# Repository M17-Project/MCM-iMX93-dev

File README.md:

[![CC BY-NC-SA 4.0][cc-by-nc-sa-shield]][cc-by-nc-sa]

# MCM-iMX93-dev
MCM-iMX93 System on Module development board.

## License
This work is licensed under a
[Creative Commons Attribution-NonCommercial-ShareAlike 4.0 International License][cc-by-nc-sa].

[![CC BY-NC-SA 4.0][cc-by-nc-sa-image]][cc-by-nc-sa]

[cc-by-nc-sa]: http://creativecommons.org/licenses/by-nc-sa/4.0/
[cc-by-nc-sa-image]: https://licensebuttons.net/l/by-nc-sa/4.0/88x31.png
[cc-by-nc-sa-shield]: https://img.shields.io/badge/License-CC%20BY--NC--SA%204.0-lightgrey.svg

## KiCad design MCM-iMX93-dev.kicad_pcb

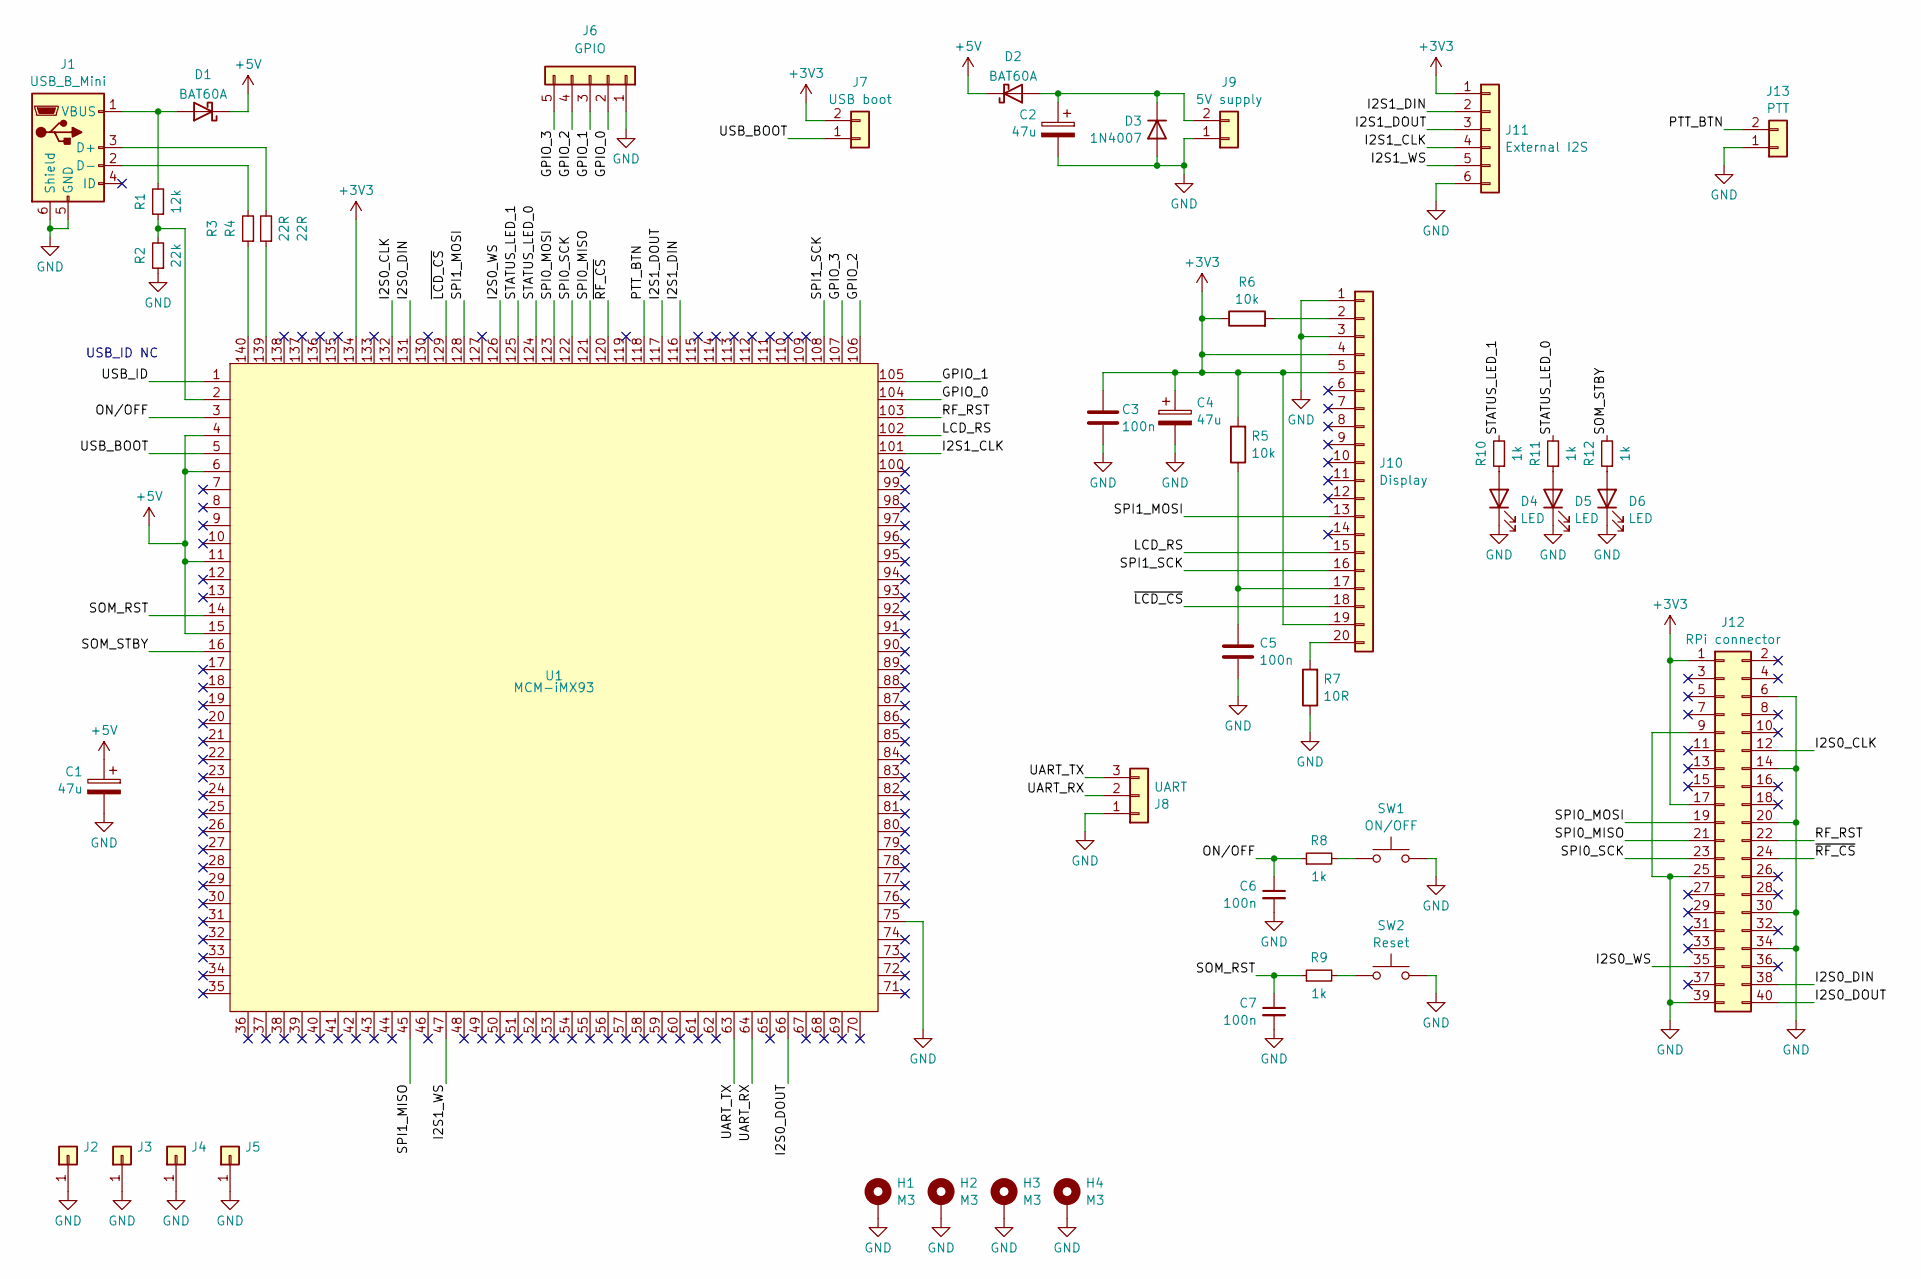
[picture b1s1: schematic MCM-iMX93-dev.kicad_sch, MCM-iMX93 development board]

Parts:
C1, C2, C4: 47u; C_Radial_D4.0mm_H5.0mm_P1.50mm
C3, C5: 100n; C_0603_1608Metric_Pad1.08x0.95mm_HandSolder
C6, C7: 100n; C_0603_1608Metric_Pad1.08x0.95mm_HandSolder; MPN C0603C104M5RAC7411
D1, D2: BAT60A; D_SOD-323; MPN Generic Schottky/10Vr/2A/SOD323-2; LCSC Part # C520634
D3: 1N4007; D_DO-41_SOD81_P10.16mm_Horizontal
D4, D5, D6: LED; LED_0603_1608Metric
H1, H2, H3, H4: M3; MountingHole_3.2mm_M3_DIN965_Pad
J1: USB_B_Mini; USB_Mini-B_Lumberg_2486_01_Horizontal
J2, J3, J4, J5: TestPoint_Pad_3.0x3.0mm
J6: GPIO; PinHeader_1x05_P2.54mm_Vertical
J7: USB boot; PinHeader_1x02_P2.54mm_Vertical
J8: UART; PinHeader_1x03_P2.54mm_Vertical
J9: 5V supply; PinHeader_1x02_P2.54mm_Vertical
J10: Display; 20x0.6_ribbon
J11: External I2S; PinHeader_1x06_P2.54mm_Vertical
J12: RPi connector; PinHeader_2x20_P2.54mm_Vertical
J13: PTT; PinHeader_1x02_P2.54mm_Vertical
R1: 12k; R_0603_1608Metric_Pad0.98x0.95mm_HandSolder
R2: 22k; R_0603_1608Metric_Pad0.98x0.95mm_HandSolder
R3, R4: 22R; R_0603_1608Metric_Pad0.98x0.95mm_HandSolder
R5, R6: 10k; R_0603_1608Metric_Pad0.98x0.95mm_HandSolder
R7: 10R; R_0603_1608Metric_Pad0.98x0.95mm_HandSolder
R8, R9, R10, R11, R12: 1k; R_0603_1608Metric_Pad0.98x0.95mm_HandSolder
SW1: ON/OFF; SW_PUSH_6mm
SW2: Reset; SW_PUSH_6mm
U1: MCM-iMX93; QFN-140_hole_small

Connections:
+3V3: C3.1, C4.1, J7.2, J10.4, J10.5, J10.19, J11.1, J12.1, J12.17, R5.2, R6.1, U1.134
+5V: C1.1, D1.1 (K), D2.1 (K), U1.4, U1.6, U1.11, U1.15
/GPIO_0: J6.2, U1.104
/GPIO_1: J6.3, U1.105
/GPIO_2: J6.4, U1.106
/GPIO_3: J6.5, U1.107
/I2S0_CLK: J12.12, U1.132
/I2S0_DIN: J12.38, U1.131
/I2S0_DOUT: J12.40, U1.66
/I2S0_WS: J12.35, U1.126
/I2S1_CLK: J11.4, U1.101
/I2S1_DIN: J11.2, U1.116
/I2S1_DOUT: J11.3, U1.117
/I2S1_WS: J11.5, U1.47
/LCD_RS: J10.15, U1.102
/ON/OFF: C6.1, R8.1, U1.3
/PTT_BTN: J13.2, U1.118
/RF_RST: J12.22, U1.103
/SOM_RST: C7.1, R9.1, U1.14
/SOM_STBY: R12.2, U1.16
/SPI0_MISO: J12.21, U1.121
/SPI0_MOSI: J12.19, U1.123
/SPI0_SCK: J12.23, U1.122
/SPI1_MISO: U1.45
/SPI1_MOSI: J10.13, U1.128
/SPI1_SCK: J10.16, U1.108
/STATUS_LED_0: R11.2, U1.124
/STATUS_LED_1: R10.2, U1.125
/UART_RX: J8.2, U1.64
/UART_TX: J8.3, U1.63
/USB_BOOT: J7.1, U1.5
/USB_ID: U1.1
/~LCD_CS: J10.18, U1.129
/~RF_CS: J12.24, U1.120
GND: C1.2, C2.2, C3.2, C4.2, C5.2, C6.2, C7.2, D3.2 (A), D4.1 (K), D5.1 (K), D6.1 (K), H1.1, H2.1, H3.1, H4.1, J1.5 (GND), J1.6 (Shield), J2.1, J3.1, J4.1, J5.1, J6.1, J8.1, J9.1, J10.1, J10.3, J11.6, J12.6, J12.9, J12.14, J12.20, J12.25, J12.30, J12.34, J12.39, J13.1, R2.1, R7.1, SW1.2, SW2.2, U1.75
unnamed: D1.2 (A), J1.1 (VBUS), R1.2
unnamed: C2.1, D2.2 (A), D3.1 (K), J9.2
unnamed: D4.2 (A), R10.1
unnamed: D5.2 (A), R11.1
unnamed: D6.2 (A), R12.1
unnamed: J1.3 (D+), R4.2
unnamed: J1.2 (D-), R3.2
unnamed: J10.2, R6.2
unnamed: C5.1, J10.17, R5.1
unnamed: J10.20, R7.2
unnamed: R1.1, R2.2, U1.2
unnamed: R3.1, U1.140
unnamed: R4.1, U1.139
unnamed: R8.2, SW1.1
unnamed: R9.2, SW2.1

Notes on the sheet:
USB_ID NC

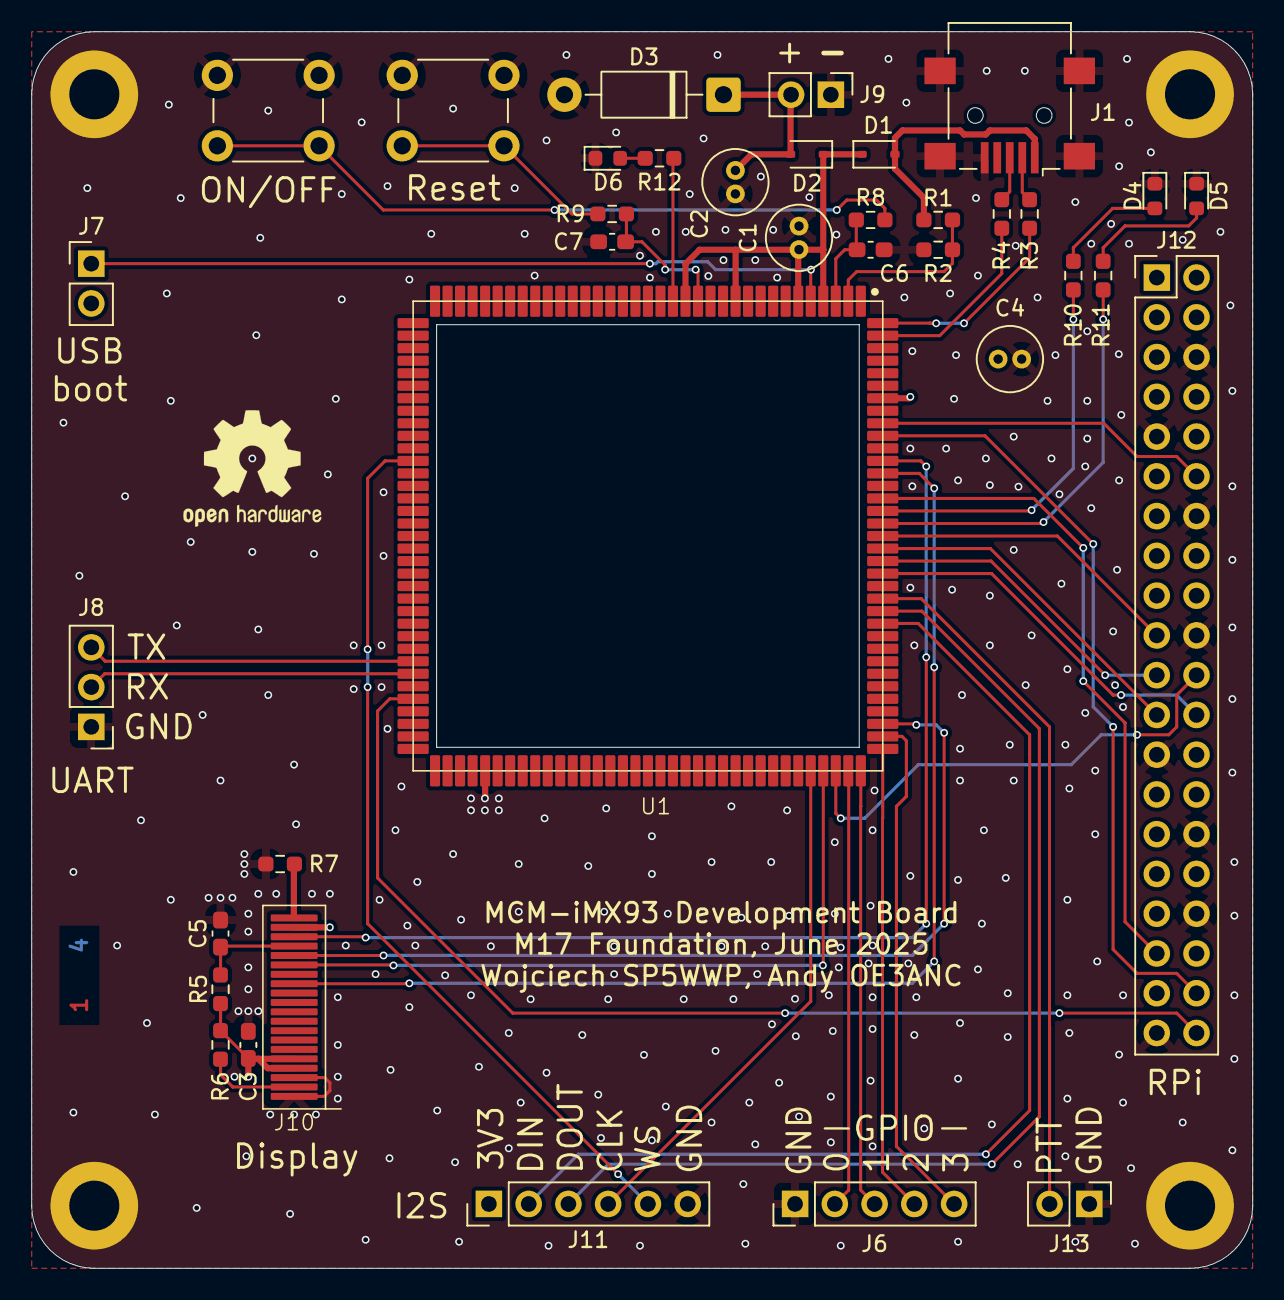
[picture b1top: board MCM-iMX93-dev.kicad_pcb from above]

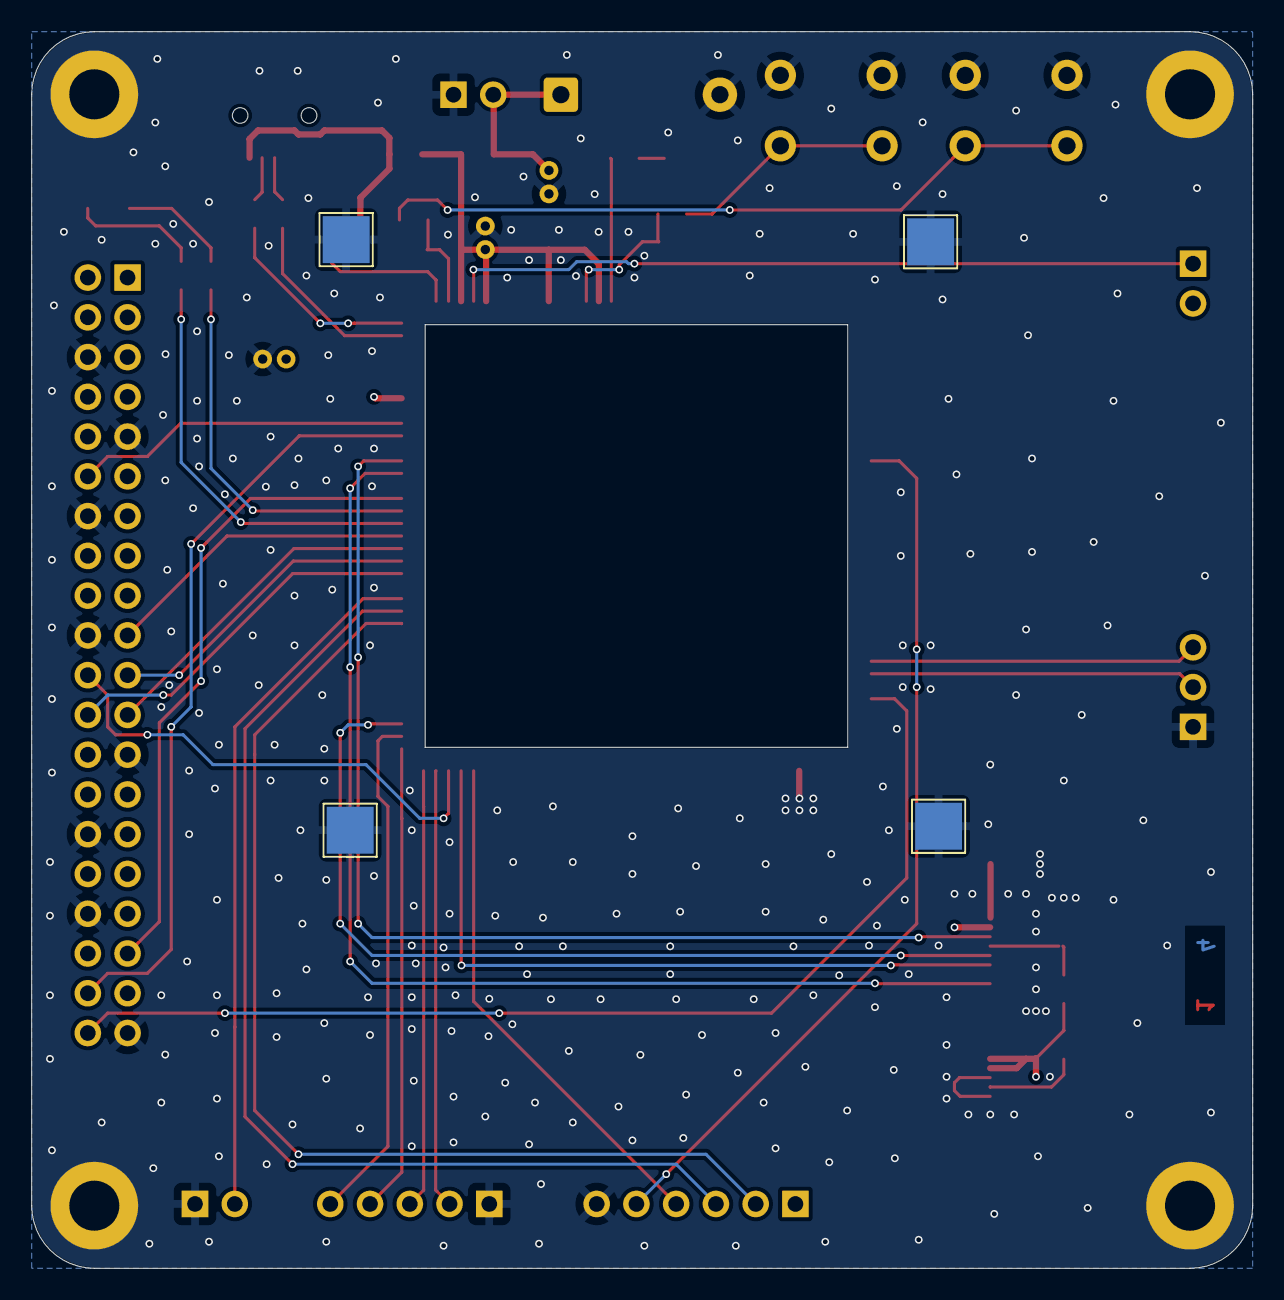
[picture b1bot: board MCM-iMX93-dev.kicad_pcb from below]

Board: 4 copper layers, 78.0 x 79.0 mm, 45 parts (4 on the bottom side), 48 nets.

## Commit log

2025-06-10 started pcb routing
2025-06-10 copper pour update
2025-06-10 fixed routing
    5V line under the USB conn
